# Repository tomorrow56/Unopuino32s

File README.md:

# Unopuino32s ESP-WROOM-32 Breakout board with CP2102

This is the uno shaped ESP32 breakout board data.

Arduino UnoフォームのESP32ブレークアウト基板です。
- ピン配置及び取り付け穴位置がUnoと同一
- Arduino IDEからの自動書込み対応
- IO電圧: 3.3V(裏面に5V入力時の分割用の抵抗パターン有)
- 電源入力電圧範囲: 4.5V～8.0V
- USB-Serial: CP2102 (Silicon Laboratories製)
- I2C接続(4pin) 0.96インチ OLED接続用コネクタ

### Web site
 https://thousandiy.wordpress.com/2017/07/05/esp-wroom-32-breakout-board-unopuino32s-cp2102-version/

### Switch Science Web Shop
 https://www.switch-science.com/catalog/3456/

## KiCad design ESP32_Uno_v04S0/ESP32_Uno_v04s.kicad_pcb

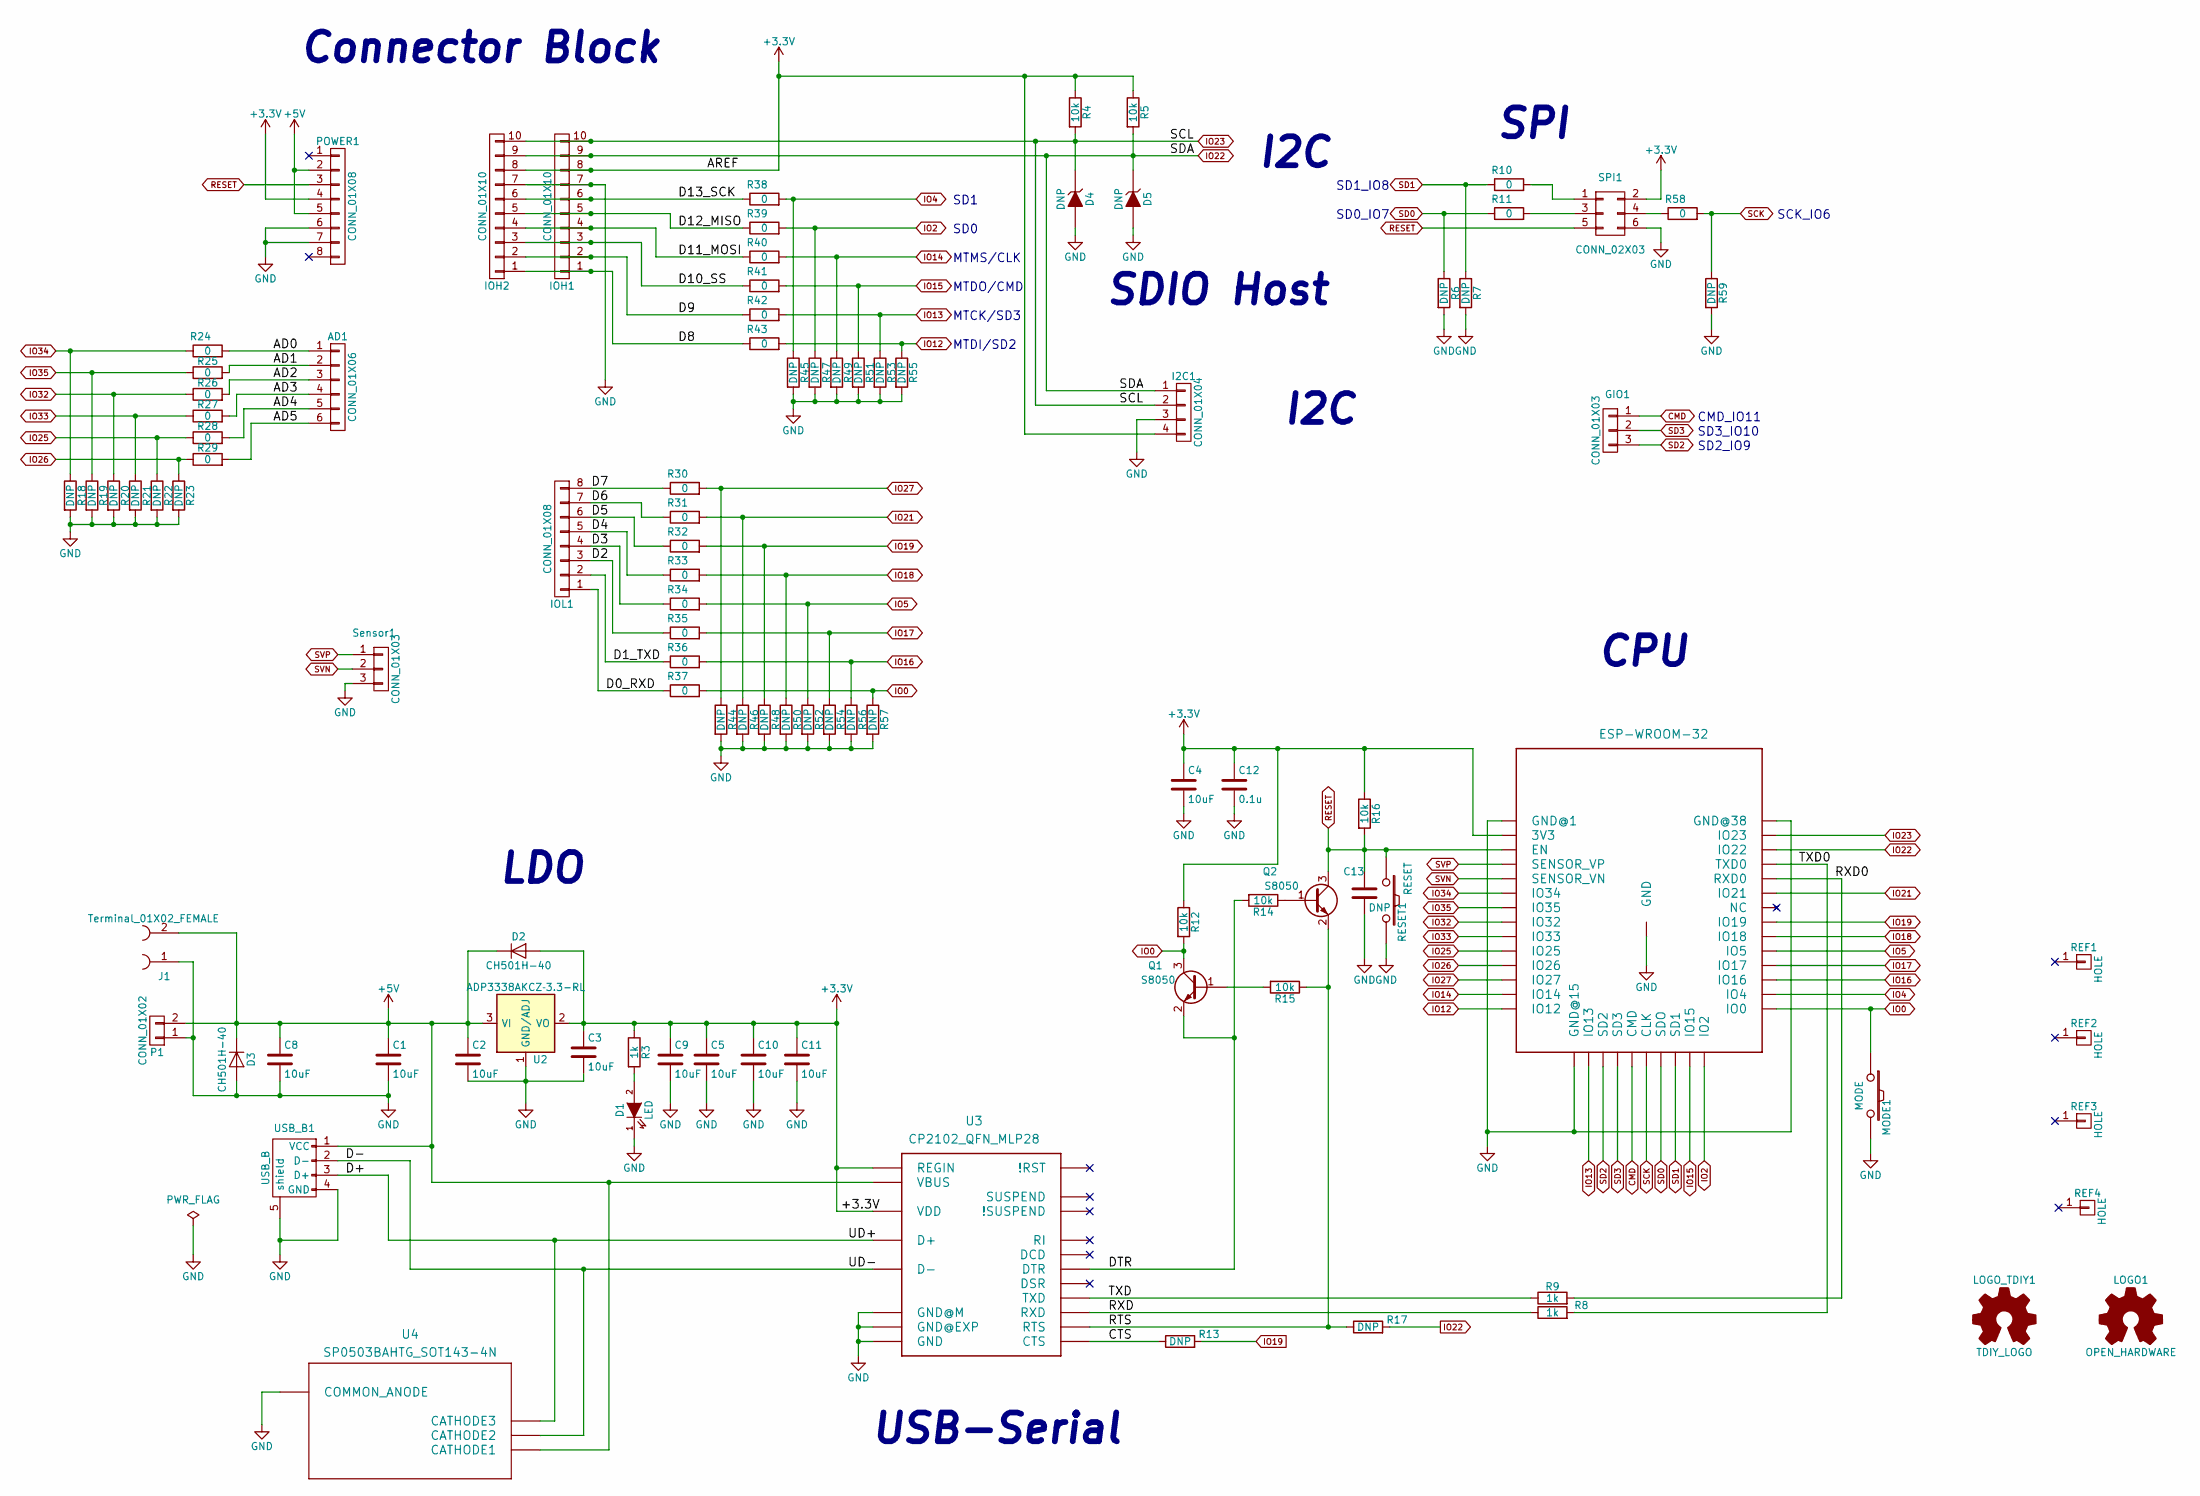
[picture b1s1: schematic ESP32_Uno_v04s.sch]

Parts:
AD1: CONN_01X06; Pin_Header_Straight_1x06_Pitch2.54mm
C1, C2, C3, C4, C5, C8, C9, C10, C11: 10uF; C_0603
C12: 0.1u; C_0603
C13: DNP; C_0603
D1: LED; LED_0805
D2, D3: CH501H-40; D_SOD-323
D4, D5: DNP; D_SOD-323
GIO1: CONN_01X03; Pin_Header_Straight_1x03_Pitch2.54mm
I2C1: CONN_01X04; Pin_Header_Straight_1x04_Pitch2.54mm
IOH1, IOH2: CONN_01X10; Pin_Header_Straight_1x10_Pitch2.54mm
IOL1: CONN_01X08; Pin_Header_Straight_1x08_Pitch2.54mm
J1: Terminal_01X02_FEMALE; Terminal_2pin_Pitch3.5mm
LOGO1: OPEN_HARDWARE; OSHW-logo_silkscreen-front_3mm
LOGO_TDIY1: TDIY_LOGO; TDIY-LOGO-S
MODE1: MODE; SW_SPST_FSMSM
P1: CONN_01X02; Pin_Header_Angled_1x02_Pitch2.54mm
POWER1: CONN_01X08; Pin_Header_Straight_1x08_Pitch2.54mm
Q1, Q2: S8050; SOT-23
R3, R8, R9: 1k; R_0603
R4, R5, R12, R14, R15, R16: 10k; R_0603
R6, R7, R18, R19, R20, R21, R22, R23, R44, R45, R46, R47, R48, R49, R50, R51, R52, R53, R54, R55, R56, R57, R59: DNP; R_0603_HandSoldering
R10, R11, R24, R25, R26, R27, R28, R29, R30, R31, R32, R33, R34, R35, R36, R37, R38, R39, R40, R41, R42, R43, R58: 0; R_0603_HandSoldering
R13, R17: DNP; R_0603
REF1, REF2, REF3, REF4: HOLE; MountingHole_3.2mm_M3
RESET1: RESET; SW_SPST_FSMSM
SPI1: CONN_02X03; Pin_Header_Straight_2x03_Pitch2.54mm
Sensor1: CONN_01X03; Pin_Header_Straight_1x03_Pitch2.54mm
U1: ESP-WROOM-32; ESP-WROOM-32_aki
U2: ADP3338AKCZ­3.3-RL; SOT-223-3Lead_TabPin2
U3: CP2102_QFN_MLP28; CP2102_MLP28
U4: SP0503BAHTG_SOT143-4N; SOT-143
USB_B1: USB_B

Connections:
+3V3: C3.1, C4.1, C5.1, C9.1, C10.1, C11.1, C12.1, D2.2 (A), I2C1.4, IOH1.8, IOH2.8, POWER1.4, R3.1, R4.1, R5.1, R12.1, R16.1, SPI1.2, U1.2 (3V3), U2.2 (VO), U3.6 (VDD), U3.7 (REGIN)
+5V: C1.1, C2.1, C8.1, D2.1 (K), D3.1 (K), J1.2, P1.2, POWER1.2, POWER1.5, U2.3 (VI), U3.8 (VBUS), U4.2 (CATHODE1), USB_B1.1 (VCC)
/AD0: AD1.1, R24.2
/AD1: AD1.2, R25.2
/AD2: AD1.3, R26.2
/AD3: AD1.4, R27.2
/AD4: AD1.5, R28.2
/AD5: AD1.6, R29.2
/CTS: R13.1, U3.23 (CTS)
/D0_RXD: IOL1.1, R37.1
/D1_TXD: IOL1.2, R36.1
/D2: IOL1.3, R35.1
/D3: IOL1.4, R34.1
/D4: IOL1.5, R33.1
/D5: IOL1.6, R32.1
/D6: IOL1.7, R31.1
/D7: IOL1.8, R30.1
/D8: IOH1.1, IOH2.1, R43.1
/D9: IOH1.2, IOH2.2, R42.1
/D10_SS: IOH1.3, IOH2.3, R41.1
/D11_MOSI: IOH1.4, IOH2.4, R40.1
/D12_MISO: IOH1.5, IOH2.5, R39.1
/D13_SCK: IOH1.6, IOH2.6, R38.1
/D+: U3.4 (D+), U4.4 (CATHODE3), USB_B1.3 (D+)
/D-: U3.5 (D-), U4.3 (CATHODE2), USB_B1.2 (D-)
/DTR: Q1.2 (E), R14.2, U3.28 (DTR)
/RTS: Q2.2 (E), R15.1, R17.1, U3.24 (RTS)
/RXD: R8.1, U3.25 (RXD)
/RXD0: R9.2, U1.34 (RXD0)
/TXD: R9.1, U3.26 (TXD)
/TXD0: R8.2, U1.35 (TXD0)
CMD: GIO1.1, U1.19 (CMD)
GND: C1.2, C2.2, C3.2, C4.2, C5.2, C8.2, C9.2, C10.2, C11.2, C12.2, C13.2, D1.1 (K), D3.2 (A), D4.2 (A), D5.2 (A), I2C1.3, IOH1.7, IOH2.7, J1.1, MODE1.2, P1.1, POWER1.6, POWER1.7, R6.2, R7.2, R18.2, R19.2, R20.2, R21.2, R22.2, R23.2, R44.2, R45.2, R46.2, R47.2, R48.2, R49.2, R50.2, R51.2, R52.2, R53.2, R54.2, R55.2, R56.2, R57.2, R59.2, RESET1.2, SPI1.6, Sensor1.3, U1.1 (GND@1), U1.15 (GND@15), U1.38 (GND@38), U1.GND, U2.1 (GND/ADJ), U3.3 (GND), U3.EXP (GND@EXP), U3.M (GND@M), U4.1 (COMMON_ANODE), USB_B1.4 (GND), USB_B1.5 (shield)
IO0: MODE1.1, Q1.3 (C), R12.2, R37.2, R57.1, U1.25 (IO0)
IO2: R39.2, R47.1, U1.24 (IO2)
IO4: R38.2, R45.1, U1.26 (IO4)
IO5: R34.2, R52.1, U1.29 (IO5)
IO12: R43.2, R55.1, U1.14 (IO12)
IO13: R42.2, R53.1, U1.16 (IO13)
IO14: R40.2, R49.1, U1.13 (IO14)
IO15: R41.2, R51.1, U1.23 (IO15)
IO16: R36.2, R56.1, U1.27 (IO16)
IO17: R35.2, R54.1, U1.28 (IO17)
IO18: R33.2, R50.1, U1.30 (IO18)
IO19: R13.2, R32.2, R48.1, U1.31 (IO19)
IO21: R31.2, R46.1, U1.33 (IO21)
IO22: D5.1 (K), I2C1.1, IOH1.9, IOH2.9, R5.2, R17.2, U1.36 (IO22)
IO23: D4.1 (K), I2C1.2, IOH1.10, IOH2.10, R4.2, U1.37 (IO23)
IO25: R22.1, R28.1, U1.10 (IO25)
IO26: R23.1, R29.1, U1.11 (IO26)
IO27: R30.2, R44.1, U1.12 (IO27)
IO32: R20.1, R26.1, U1.8 (IO32)
IO33: R21.1, R27.1, U1.9 (IO33)
IO34: R18.1, R24.1, U1.6 (IO34)
IO35: R19.1, R25.1, U1.7 (IO35)
unnamed: D1.2 (A), R3.2
unnamed: Q1.1 (B), R15.2
unnamed: Q2.1 (B), R14.1
unnamed: R10.2, SPI1.1
unnamed: R11.2, SPI1.3
unnamed: R58.1, SPI1.4
RESET: C13.1, POWER1.3, Q2.3 (C), R16.2, RESET1.1, SPI1.5, U1.3 (EN)
SCK: R58.2, R59.1, U1.20 (CLK)
SD0: R6.1, R11.1, U1.21 (SDO)
SD1: R7.1, R10.1, U1.22 (SD1)
SD2: GIO1.3, U1.17 (SD2)
SD3: GIO1.2, U1.18 (SD3)
SVN: Sensor1.2, U1.5 (SENSOR_VN)
SVP: Sensor1.1, U1.4 (SENSOR_VP)

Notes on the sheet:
Connector Block
LDO
USB-Serial
CPU
SPI
SDIO Host
MTDI/SD2
MTCK/SD3
MTDO/CMD
MTMS/CLK
SD0
SD1
SD0_IO7
SD1_IO8
SD2_IO9
SD3_IO10
CMD_IO11
SCK_IO6
I2C

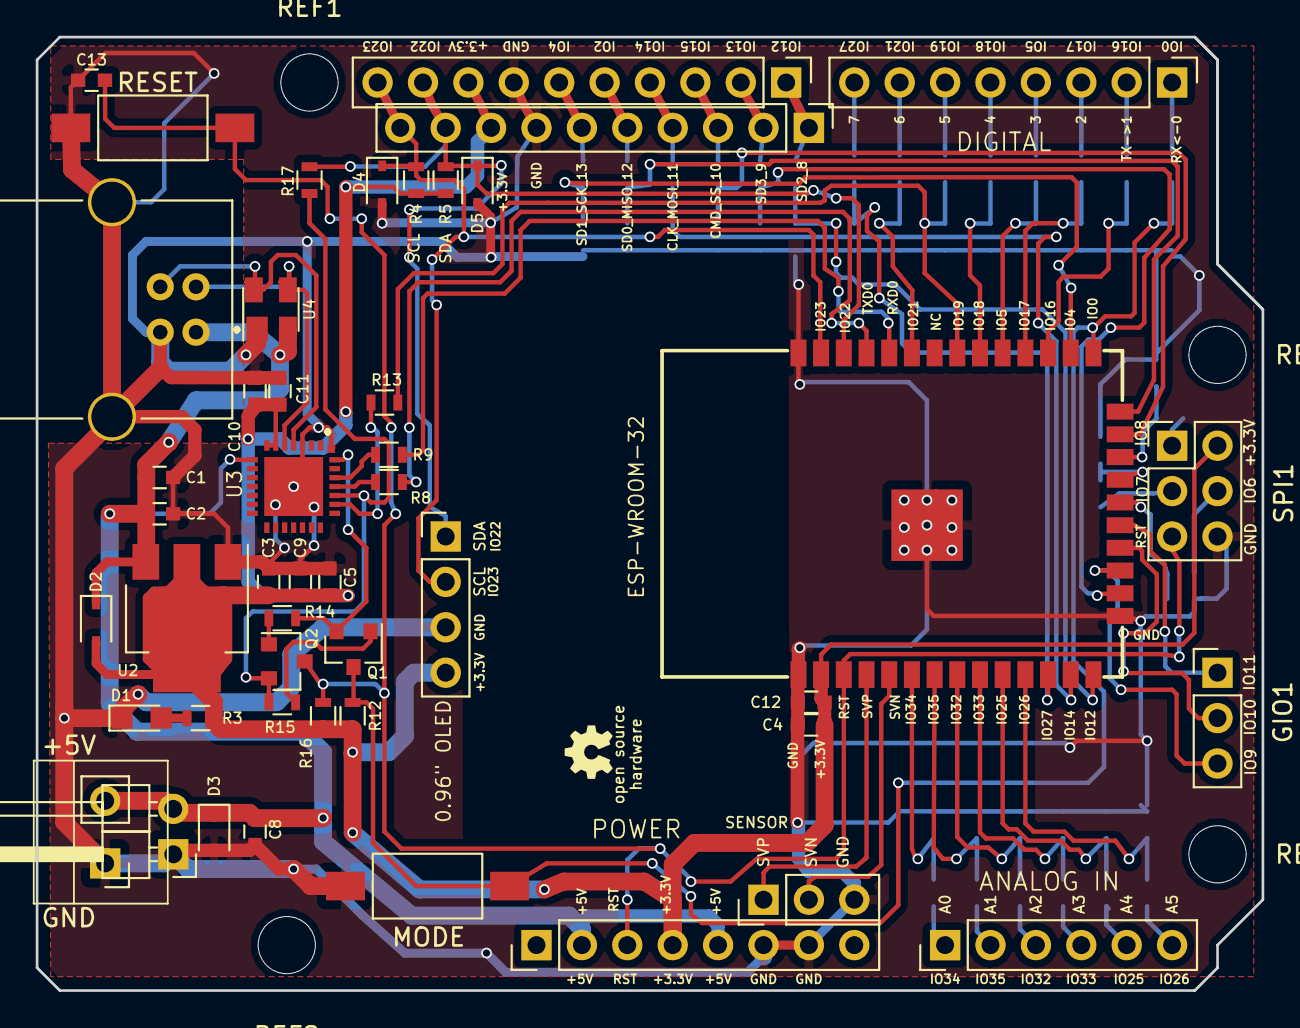
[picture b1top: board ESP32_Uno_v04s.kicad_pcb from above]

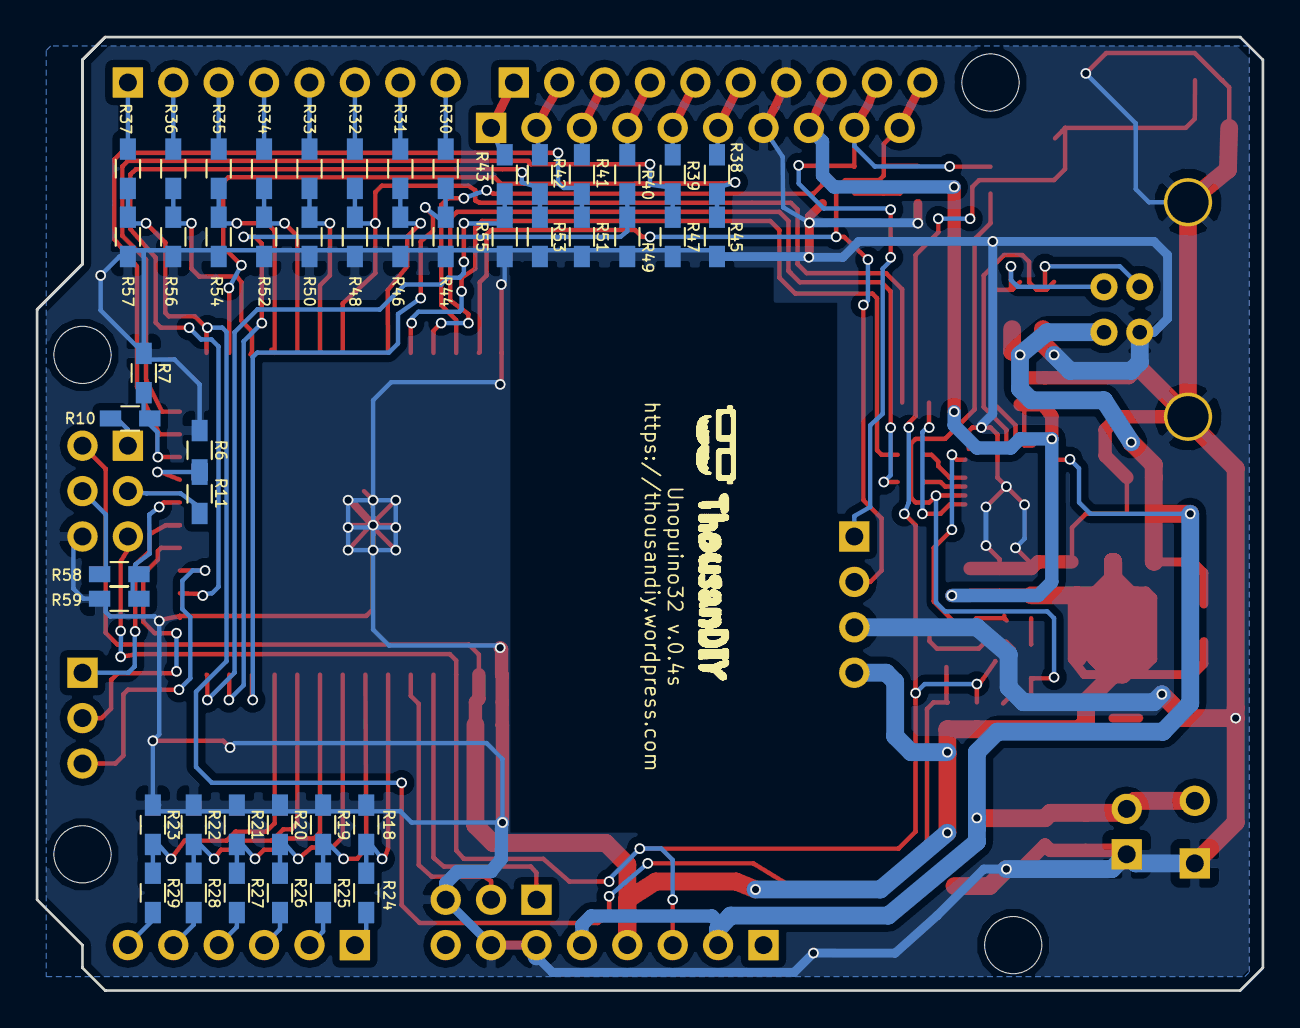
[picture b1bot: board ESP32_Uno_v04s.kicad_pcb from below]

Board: 2 copper layers, 68.6 x 53.3 mm, 99 parts (47 on the bottom side), 69 nets.

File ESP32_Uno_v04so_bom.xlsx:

Reference | Value | Footprint | side
C1 | 10uF | Capacitors_SMD:C_0603
C2 | 10uF | Capacitors_SMD:C_0603
C3 | 10uF | Capacitors_SMD:C_0603
C4 | 10uF | Capacitors_SMD:C_0603
C5 | 10uF | Capacitors_SMD:C_0603
C8 | 10uF | Capacitors_SMD:C_0603
C9 | 10uF | Capacitors_SMD:C_0603
C10 | 10uF | Capacitors_SMD:C_0603
C11 | 10uF | Capacitors_SMD:C_0603
C12 | 0.1u | Capacitors_SMD:C_0603
C13 | DNP | Capacitors_SMD:C_0603 | DNP
D1 | LED | LEDs:LED_0805
D2 | CH501H-40 | Diodes_SMD:D_SOD-323
D3 | CH501H-40 | Diodes_SMD:D_SOD-323
D4 | DNP | Diodes_SMD:D_SOD-323 | DNP
D5 | DNP | Diodes_SMD:D_SOD-323 | DNP
Q1 | S8050 | TO_SOT_Packages_SMD:SOT-23
Q2 | S8050 | TO_SOT_Packages_SMD:SOT-23
R3 | 1k | Resistors_SMD:R_0603
R4 | 10k | Resistors_SMD:R_0603
R5 | 10k | Resistors_SMD:R_0603
R6 | DNP | Resistors_SMD:R_0603_HandSoldering | DNP
R7 | DNP | Resistors_SMD:R_0603_HandSoldering | DNP
R8 | 1k | Resistors_SMD:R_0603
R9 | 1k | Resistors_SMD:R_0603
R10 | 0 | Resistors_SMD:R_0603_HandSoldering | DNP
R11 | 0 | Resistors_SMD:R_0603_HandSoldering | DNP
R12 | 10k | Resistors_SMD:R_0603
R13 | DNP | Resistors_SMD:R_0603 | DNP
R14 | 10k | Resistors_SMD:R_0603
R15 | 10k | Resistors_SMD:R_0603
R16 | 10k | Resistors_SMD:R_0603
R17 | DNP | Resistors_SMD:R_0603 | DNP
R18 | DNP | Resistors_SMD:R_0603_HandSoldering | DNP
R19 | DNP | Resistors_SMD:R_0603_HandSoldering | DNP
R20 | DNP | Resistors_SMD:R_0603_HandSoldering | DNP
R21 | DNP | Resistors_SMD:R_0603_HandSoldering | DNP
R22 | DNP | Resistors_SMD:R_0603_HandSoldering | DNP
R23 | DNP | Resistors_SMD:R_0603_HandSoldering | DNP
R24 | 0 | Resistors_SMD:R_0603_HandSoldering
R25 | 0 | Resistors_SMD:R_0603_HandSoldering
R26 | 0 | Resistors_SMD:R_0603_HandSoldering
R27 | 0 | Resistors_SMD:R_0603_HandSoldering
R28 | 0 | Resistors_SMD:R_0603_HandSoldering
R29 | 0 | Resistors_SMD:R_0603_HandSoldering
R30 | 0 | Resistors_SMD:R_0603_HandSoldering
R31 | 0 | Resistors_SMD:R_0603_HandSoldering
R32 | 0 | Resistors_SMD:R_0603_HandSoldering
R33 | 0 | Resistors_SMD:R_0603_HandSoldering
R34 | 0 | Resistors_SMD:R_0603_HandSoldering
R35 | 0 | Resistors_SMD:R_0603_HandSoldering
R36 | 0 | Resistors_SMD:R_0603_HandSoldering
R37 | 0 | Resistors_SMD:R_0603_HandSoldering
R38 | 0 | Resistors_SMD:R_0603_HandSoldering
R39 | 0 | Resistors_SMD:R_0603_HandSoldering
R40 | 0 | Resistors_SMD:R_0603_HandSoldering
R41 | 0 | Resistors_SMD:R_0603_HandSoldering
R42 | 0 | Resistors_SMD:R_0603_HandSoldering
R43 | 0 | Resistors_SMD:R_0603_HandSoldering
R44 | DNP | Resistors_SMD:R_0603_HandSoldering | DNP
R45 | DNP | Resistors_SMD:R_0603_HandSoldering | DNP
R46 | DNP | Resistors_SMD:R_0603_HandSoldering | DNP
R47 | DNP | Resistors_SMD:R_0603_HandSoldering | DNP
R48 | DNP | Resistors_SMD:R_0603_HandSoldering | DNP
R49 | DNP | Resistors_SMD:R_0603_HandSoldering | DNP
R50 | DNP | Resistors_SMD:R_0603_HandSoldering | DNP
R51 | DNP | Resistors_SMD:R_0603_HandSoldering | DNP
R52 | DNP | Resistors_SMD:R_0603_HandSoldering | DNP
R53 | DNP | Resistors_SMD:R_0603_HandSoldering | DNP
R54 | DNP | Resistors_SMD:R_0603_HandSoldering | DNP
R55 | DNP | Resistors_SMD:R_0603_HandSoldering | DNP
R56 | DNP | Resistors_SMD:R_0603_HandSoldering | DNP
R57 | DNP | Resistors_SMD:R_0603_HandSoldering | DNP
R58 | 0 | Resistors_SMD:R_0603_HandSoldering | DNP
R59 | DNP | Resistors_SMD:R_0603_HandSoldering | DNP
MODE1 | MODE | Buttons_Switches_SMD:SW_SPST_FSMSM
RESET1 | RESET | Buttons_Switches_SMD:SW_SPST_FSMSM
U1 | ESP-WROOM-32 | footprint:ESP-WROOM-32_aki
U2 | ADP3338AKCZ3.3-RL | TO_SOT_Packages_SMD:SOT-223-3Lead_TabPin2
U3 | CP2102_QFN_MLP28 | footprint:CP2102_MLP28
U4 | SP0503BAHTG_SOT143-4N | TO_SOT_Packages_SMD:SOT-143
AD1 | CONN_01X06 | Pin_Headers:Pin_Header_Straight_1x06_Pitch2.54mm
GIO1 | CONN_01X03 | Pin_Headers:Pin_Header_Straight_1x03_Pitch2.54mm | DNP
I2C1 | CONN_01X04 | Pin_Headers:Pin_Header_Straight_1x04_Pitch2.54mm
IOH1 | CONN_01X10 | Pin_Headers:Pin_Header_Straight_1x10_Pitch2.54mm
IOH2 | CONN_01X10 | Pin_Headers:Pin_Header_Straight_1x10_Pitch2.54mm
IOL1 | CONN_01X08 | Pin_Headers:Pin_Header_Straight_1x08_Pitch2.54mm
Sensor1 | CONN_01X03 | Pin_Headers:Pin_Header_Straight_1x03_Pitch2.54mm
SPI1 | CONN_02X03 | Pin_Headers:Pin_Header_Straight_2x03_Pitch2.54mm | DNP
P1 | CONN_01X02 | Pin_Headers:Pin_Header_Angled_1x02_Pitch2.54mm
POWER1 | CONN_01X08 | Pin_Headers:Pin_Header_Straight_1x08_Pitch2.54mm
J1 | Terminal_01X02_FEMALE | footprint:Terminal_2pin_Pitch3.5mm
USB_B1 | USB_B | Connect:USB_B
REF1 | HOLE | Mounting_Holes:MountingHole_3.2mm_M3
REF2 | HOLE | Mounting_Holes:MountingHole_3.2mm_M3
REF3 | HOLE | Mounting_Holes:MountingHole_3.2mm_M3
REF4 | HOLE | Mounting_Holes:MountingHole_3.2mm_M3
LOGO_TDIY1 | TDIY_LOGO | footprint:TDIY-LOGO-S
LOGO1 | OPEN_HARDWARE | footprint:OSHW-logo_silkscreen-front_3mm

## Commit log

2018-02-22 Switch Science version
2018-02-23 add optional component library
2018-02-23 change to use original component
2018-07-18 Add pin_Label
2019-04-29 Organize the repository
